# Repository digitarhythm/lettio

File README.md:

# Lettio
TReK Lettio KiCAD Project

[Firmware repository](https://github.com/digitarhythm/vial-qmk/tree/digitarhythm/keyboards/trek/lettio)

## Schematics
[Schematics PDF](https://github.com/digitarhythm/lettio/blob/main/pcb/lettio_pcb_rev1.0/resouces/lettio_pcb.pdf)

## Build sample image

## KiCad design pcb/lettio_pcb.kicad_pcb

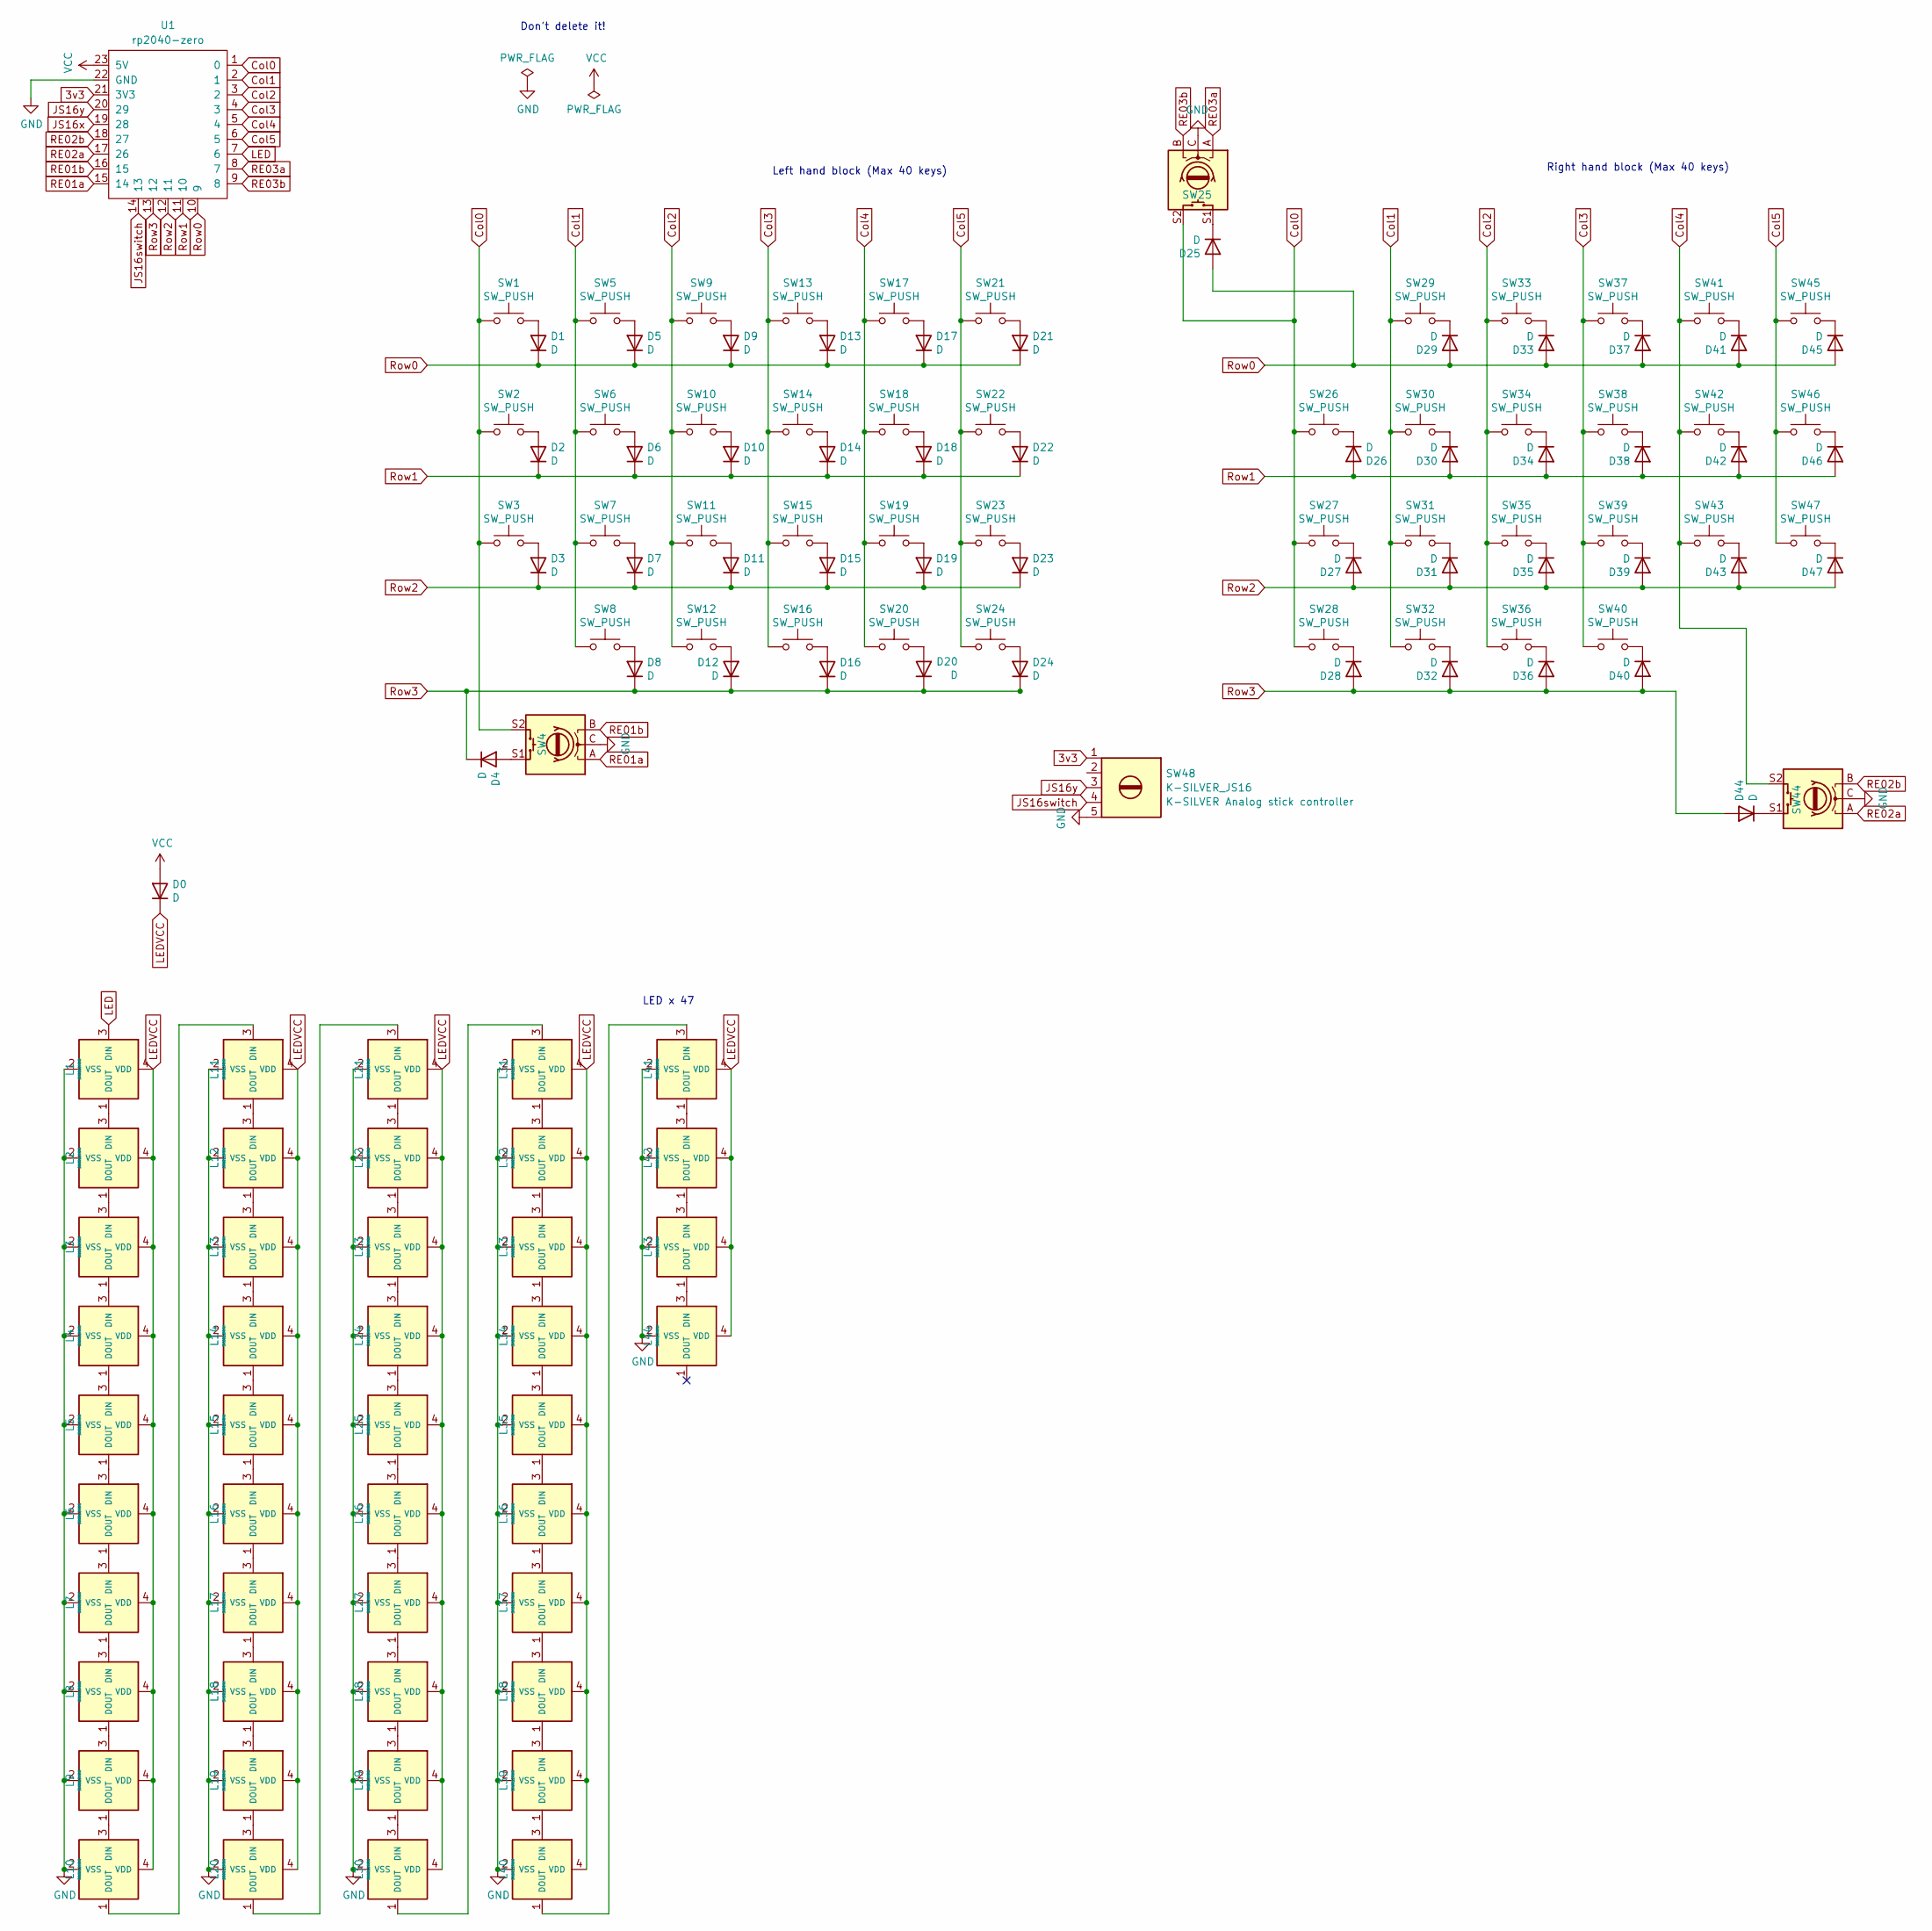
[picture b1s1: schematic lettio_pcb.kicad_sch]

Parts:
D0, D1, D2, D3, D4, D5, D6, D7, D8, D9, D10, D11, D12, D13, D14, D15, D16, D17, D18, D19, D20, D21, D22, D23, D24, D25, D26, D27, D28, D29, D30, D31, D32, D33, D34, D35, D36, D37, D38, D39, D40, D41, D42, D43, D44, D45, D46, D47: D; Diode_SMD
L1, L2, L3, L4, L5, L6, L7, L8, L9, L10, L11, L12, L13, L14, L15, L16, L17, L18, L19, L20, L21, L22, L23, L24, L25, L26, L27, L28, L29, L30, L31, L32, L33, L34, L35, L36, L37, L38, L39, L40, L41, L42, L43, L44: SK6812MINI; LED_SK6812MINI-E_BL
SW1, SW2, SW3, SW5, SW6, SW7, SW8, SW9, SW10, SW11, SW12, SW13, SW14, SW15, SW16, SW17, SW18, SW19, SW20, SW21, SW22, SW23, SW24, SW26, SW27, SW28, SW29, SW30, SW31, SW32, SW33, SW34, SW35, SW36, SW37, SW38, SW39, SW40, SW41, SW42, SW43, SW45, SW46, SW47: SW_PUSH; Choc_v1v2_Hotswap_1u(short_pad)
SW4, SW44: RotaryEncoder_Switch; RotaryEncoder_EC12E
SW25: RotaryEncoder_EC12E
SW48: K-SILVER_JS16; K-SILVER JS16
U1: rp2040-zero; rp2040-zero(THonly)

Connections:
3v3: SW48.1, U1.21 (3V3)
Col0: SW1.1, SW2.1, SW3.1, SW4.S2, SW25.S2, SW26.1, SW27.1, SW28.1, U1.1 (0)
Col1: SW5.1, SW6.1, SW7.1, SW8.1, SW29.1, SW30.1, SW31.1, SW32.1, U1.2 (1)
Col2: SW9.1, SW10.1, SW11.1, SW12.2, SW33.1, SW34.1, SW35.1, SW36.1, U1.3 (2)
Col3: SW13.1, SW14.1, SW15.1, SW16.1, SW37.1, SW38.1, SW39.1, SW40.1, U1.4 (3)
Col4: SW17.1, SW18.1, SW19.1, SW20.2, SW41.1, SW42.1, SW43.1, SW44.S2, U1.5 (4)
Col5: SW21.1, SW22.1, SW23.1, SW24.1, SW45.1, SW46.1, SW47.1, U1.6 (5)
GND: L1.2 (VSS), L2.2 (VSS), L3.2 (VSS), L4.2 (VSS), L5.2 (VSS), L6.2 (VSS), L7.2 (VSS), L8.2 (VSS), L9.2 (VSS), L10.2 (VSS), L11.2 (VSS), L12.2 (VSS), L13.2 (VSS), L14.2 (VSS), L15.2 (VSS), L16.2 (VSS), L17.2 (VSS), L18.2 (VSS), L19.2 (VSS), L20.2 (VSS), L21.2 (VSS), L22.2 (VSS), L23.2 (VSS), L24.2 (VSS), L25.2 (VSS), L26.2 (VSS), L27.2 (VSS), L28.2 (VSS), L29.2 (VSS), L30.2 (VSS), L31.2 (VSS), L32.2 (VSS), L33.2 (VSS), L34.2 (VSS), L35.2 (VSS), L36.2 (VSS), L37.2 (VSS), L38.2 (VSS), L39.2 (VSS), L40.2 (VSS), L41.2 (VSS), L42.2 (VSS), L43.2 (VSS), L44.2 (VSS), SW4.C, SW25.C, SW44.C, SW48.5, U1.22 (GND)
JS16switch: SW48.4, U1.14 (13)
JS16x: U1.19 (28)
JS16y: SW48.3, U1.20 (29)
LED: L1.3 (DIN), U1.7 (6)
LEDVCC: D0.1 (K), L1.4 (VDD), L2.4 (VDD), L3.4 (VDD), L4.4 (VDD), L5.4 (VDD), L6.4 (VDD), L7.4 (VDD), L8.4 (VDD), L9.4 (VDD), L10.4 (VDD), L11.4 (VDD), L12.4 (VDD), L13.4 (VDD), L14.4 (VDD), L15.4 (VDD), L16.4 (VDD), L17.4 (VDD), L18.4 (VDD), L19.4 (VDD), L20.4 (VDD), L21.4 (VDD), L22.4 (VDD), L23.4 (VDD), L24.4 (VDD), L25.4 (VDD), L26.4 (VDD), L27.4 (VDD), L28.4 (VDD), L29.4 (VDD), L30.4 (VDD), L31.4 (VDD), L32.4 (VDD), L33.4 (VDD), L34.4 (VDD), L35.4 (VDD), L36.4 (VDD), L37.4 (VDD), L38.4 (VDD), L39.4 (VDD), L40.4 (VDD), L41.4 (VDD), L42.4 (VDD), L43.4 (VDD), L44.4 (VDD)
unnamed: D1.2 (A), SW1.2
unnamed: D2.2 (A), SW2.2
unnamed: D3.2 (A), SW3.2
unnamed: D4.2 (A), SW4.S1
unnamed: D5.2 (A), SW5.2
unnamed: D6.2 (A), SW6.2
unnamed: D7.2 (A), SW7.2
unnamed: D8.2 (A), SW8.2
unnamed: D9.2 (A), SW9.2
unnamed: D10.2 (A), SW10.2
unnamed: D11.2 (A), SW11.2
unnamed: D12.2 (A), SW12.1
unnamed: D13.2 (A), SW13.2
unnamed: D14.2 (A), SW14.2
unnamed: D15.2 (A), SW15.2
unnamed: D16.2 (A), SW16.2
unnamed: D17.2 (A), SW17.2
unnamed: D18.2 (A), SW18.2
unnamed: D19.2 (A), SW19.2
unnamed: D20.2 (A), SW20.1
unnamed: D21.2 (A), SW21.2
unnamed: D22.2 (A), SW22.2
unnamed: D23.2 (A), SW23.2
unnamed: D24.2 (A), SW24.2
unnamed: D25.1 (K), SW25.S1
unnamed: D26.1 (K), SW26.2
unnamed: D27.1 (K), SW27.2
unnamed: D28.1 (K), SW28.2
unnamed: D29.1 (K), SW29.2
unnamed: D30.1 (K), SW30.2
unnamed: D31.1 (K), SW31.2
unnamed: D32.1 (K), SW32.2
unnamed: D33.1 (K), SW33.2
unnamed: D34.1 (K), SW34.2
unnamed: D35.1 (K), SW35.2
unnamed: D36.1 (K), SW36.2
unnamed: D37.1 (K), SW37.2
unnamed: D38.1 (K), SW38.2
unnamed: D39.1 (K), SW39.2
unnamed: D40.1 (K), SW40.2
unnamed: D41.1 (K), SW41.2
unnamed: D42.1 (K), SW42.2
unnamed: D43.1 (K), SW43.2
unnamed: D44.1 (K), SW44.S1
unnamed: D45.1 (K), SW45.2
unnamed: D46.1 (K), SW46.2
unnamed: D47.1 (K), SW47.2
unnamed: L1.1 (DOUT), L2.3 (DIN)
unnamed: L2.1 (DOUT), L3.3 (DIN)
unnamed: L3.1 (DOUT), L4.3 (DIN)
unnamed: L4.1 (DOUT), L5.3 (DIN)
unnamed: L5.1 (DOUT), L6.3 (DIN)
unnamed: L6.1 (DOUT), L7.3 (DIN)
unnamed: L7.1 (DOUT), L8.3 (DIN)
unnamed: L8.1 (DOUT), L9.3 (DIN)
unnamed: L9.1 (DOUT), L10.3 (DIN)
unnamed: L10.1 (DOUT), L11.3 (DIN)
unnamed: L11.1 (DOUT), L12.3 (DIN)
unnamed: L12.1 (DOUT), L13.3 (DIN)
unnamed: L13.1 (DOUT), L14.3 (DIN)
unnamed: L14.1 (DOUT), L15.3 (DIN)
unnamed: L15.1 (DOUT), L16.3 (DIN)
unnamed: L16.1 (DOUT), L17.3 (DIN)
unnamed: L17.1 (DOUT), L18.3 (DIN)
unnamed: L18.1 (DOUT), L19.3 (DIN)
unnamed: L19.1 (DOUT), L20.3 (DIN)
unnamed: L20.1 (DOUT), L21.3 (DIN)
unnamed: L21.1 (DOUT), L22.3 (DIN)
unnamed: L22.1 (DOUT), L23.3 (DIN)
unnamed: L23.1 (DOUT), L24.3 (DIN)
unnamed: L24.1 (DOUT), L25.3 (DIN)
unnamed: L25.1 (DOUT), L26.3 (DIN)
unnamed: L26.1 (DOUT), L27.3 (DIN)
unnamed: L27.1 (DOUT), L28.3 (DIN)
unnamed: L28.1 (DOUT), L29.3 (DIN)
unnamed: L29.1 (DOUT), L30.3 (DIN)
unnamed: L30.1 (DOUT), L31.3 (DIN)
unnamed: L31.1 (DOUT), L32.3 (DIN)
unnamed: L32.1 (DOUT), L33.3 (DIN)
unnamed: L33.1 (DOUT), L34.3 (DIN)
unnamed: L34.1 (DOUT), L35.3 (DIN)
unnamed: L35.1 (DOUT), L36.3 (DIN)
unnamed: L36.1 (DOUT), L37.3 (DIN)
unnamed: L37.1 (DOUT), L38.3 (DIN)
unnamed: L38.1 (DOUT), L39.3 (DIN)
unnamed: L39.1 (DOUT), L40.3 (DIN)
unnamed: L40.1 (DOUT), L41.3 (DIN)
unnamed: L41.1 (DOUT), L42.3 (DIN)
unnamed: L42.1 (DOUT), L43.3 (DIN)
unnamed: L43.1 (DOUT), L44.3 (DIN)
RE01a: SW4.A, U1.15 (14)
RE01b: SW4.B, U1.16 (15)
RE02a: SW44.A, U1.17 (26)
RE02b: SW44.B, U1.18 (27)
RE03a: SW25.A, U1.8 (7)
RE03b: SW25.B, U1.9 (8)
Row0: D1.1 (K), D5.1 (K), D9.1 (K), D13.1 (K), D17.1 (K), D21.1 (K), D25.2 (A), D29.2 (A), D33.2 (A), D37.2 (A), D41.2 (A), D45.2 (A), U1.10 (9)
Row1: D2.1 (K), D6.1 (K), D10.1 (K), D14.1 (K), D18.1 (K), D22.1 (K), D26.2 (A), D30.2 (A), D34.2 (A), D38.2 (A), D42.2 (A), D46.2 (A), U1.11 (10)
Row2: D3.1 (K), D7.1 (K), D11.1 (K), D15.1 (K), D19.1 (K), D23.1 (K), D27.2 (A), D31.2 (A), D35.2 (A), D39.2 (A), D43.2 (A), D47.2 (A), U1.12 (11)
Row3: D4.1 (K), D8.1 (K), D12.1 (K), D16.1 (K), D20.1 (K), D24.1 (K), D28.2 (A), D32.2 (A), D36.2 (A), D40.2 (A), D44.2 (A), U1.13 (12)
VCC: D0.2 (A), U1.23 (5V)

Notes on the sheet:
Left hand block (Max 40 keys)
LED x 47
Don't delete it!
Right hand block (Max 40 keys)

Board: 2 copper layers, 141 parts (0 on the bottom side), 113 nets, no tracks yet.

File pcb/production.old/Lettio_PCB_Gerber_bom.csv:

Designator,Footprint,Quantity,Value,LCSC Part #
"D0, D1, D10, D11, D12, D13, D14, D15, D16, D17, D18, D19, D2, D20, D21, D22, D23, D24, D25, D26, D27, D28, D29, D3, D30, D31, D32, D33, D34, D35, D36, D37, D38, D39, D4, D40, D41, D42, D43, D44, D45, D46, D47, D5, D6, D7, D8, D9",Diode_SMD,48,D,
"L1, L10, L11, L12, L13, L14, L15, L16, L17, L18, L19, L2, L20, L21, L22, L23, L24, L25, L26, L27, L28, L29, L3, L30, L31, L32, L33, L34, L35, L36, L37, L38, L39, L4, L40, L41, L42, L43, L44, L5, L6, L7, L8, L9",LED_SK6812MINI-E_BL,44,SK6812MINI,
"ROTARYENCODER_SWITCH_3, ROTARYENCODER_SWITCH_2, ROTARYENCODER_SWITCH",RotaryEncoder_EC12E,3,,
"SW1, SW10, SW11, SW12, SW13, SW14, SW15, SW16, SW17, SW18, SW19, SW2, SW20, SW21, SW22, SW23, SW24, SW26, SW27, SW28, SW29, SW3, SW30, SW31, SW32, SW33, SW34, SW35, SW36, SW37, SW38, SW39, SW40, SW41, SW42, SW43, SW45, SW46, SW47, SW5, SW6, SW7, SW8, SW9",Choc_v1v2_Hotswap_1u(short_pad),44,SW_PUSH,
SW48,K-SILVER JS16,1,K-SILVER_JS16,
U1,rp2040-zero(THonly),1,rp2040-zero,
